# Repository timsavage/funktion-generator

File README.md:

##################
Funktion-generator
##################

AVR based function generator - Hardware + Firmware

Full project details at https://hackaday.io/project/19866

See sub folders for README docs on sub-components.

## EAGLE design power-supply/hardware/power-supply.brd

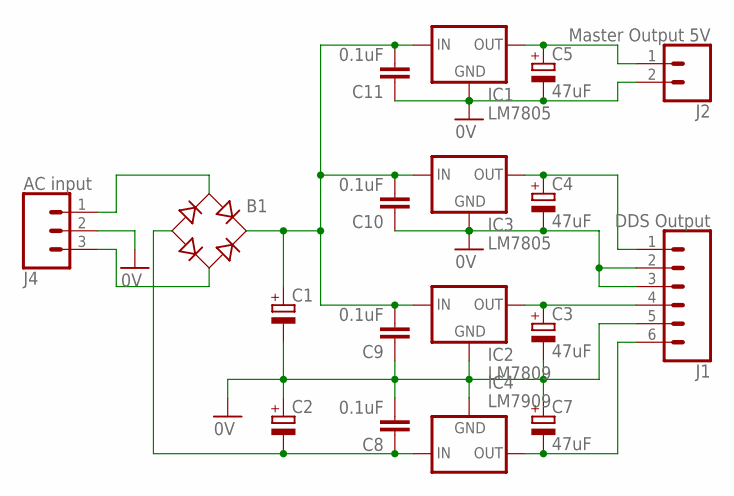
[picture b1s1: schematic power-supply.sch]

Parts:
B1: RB1A
C1, C2: CPOL-EUE7.5-16; E7,5-16
C3, C4, C7: 47uF; E5-6
C5: 47uF; E2,5-6
C8, C9, C10, C11: 0.1uF; C025-025X050
IC1, IC3: LM7805; 78XXS
IC2: LM7809; 78XXS
IC4: LM7909; 79XXS
J1: DDS Output; MOLEX-1X6
J2: Master Output 5V; MOLEX-1X2
J4: AC input; MOLEX-1X3

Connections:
0V: C1.-, C2.+, C3.-, C4.-, C5.-, C7.+, C8.2, C9.1, C10.1, C11.1, IC1.GND, IC2.GND, IC3.GND, IC4.GND, J1.2, J1.3, J1.5, J2.2, J4.2
5V-DDS: C4.+, IC3.OUT, J1.1
5V-MASTER: C5.+, IC1.OUT, J2.1
9V: C3.+, IC2.OUT, J1.4
-9V: C7.-, IC4.OUT, J1.6
unnamed: B1.+, C1.+, C9.2, C10.2, C11.2, IC1.IN, IC2.IN, IC3.IN
unnamed: B1.-, C2.-, C8.1, IC4.IN
unnamed: B1.AC2, J4.3
unnamed: B1.AC1, J4.1

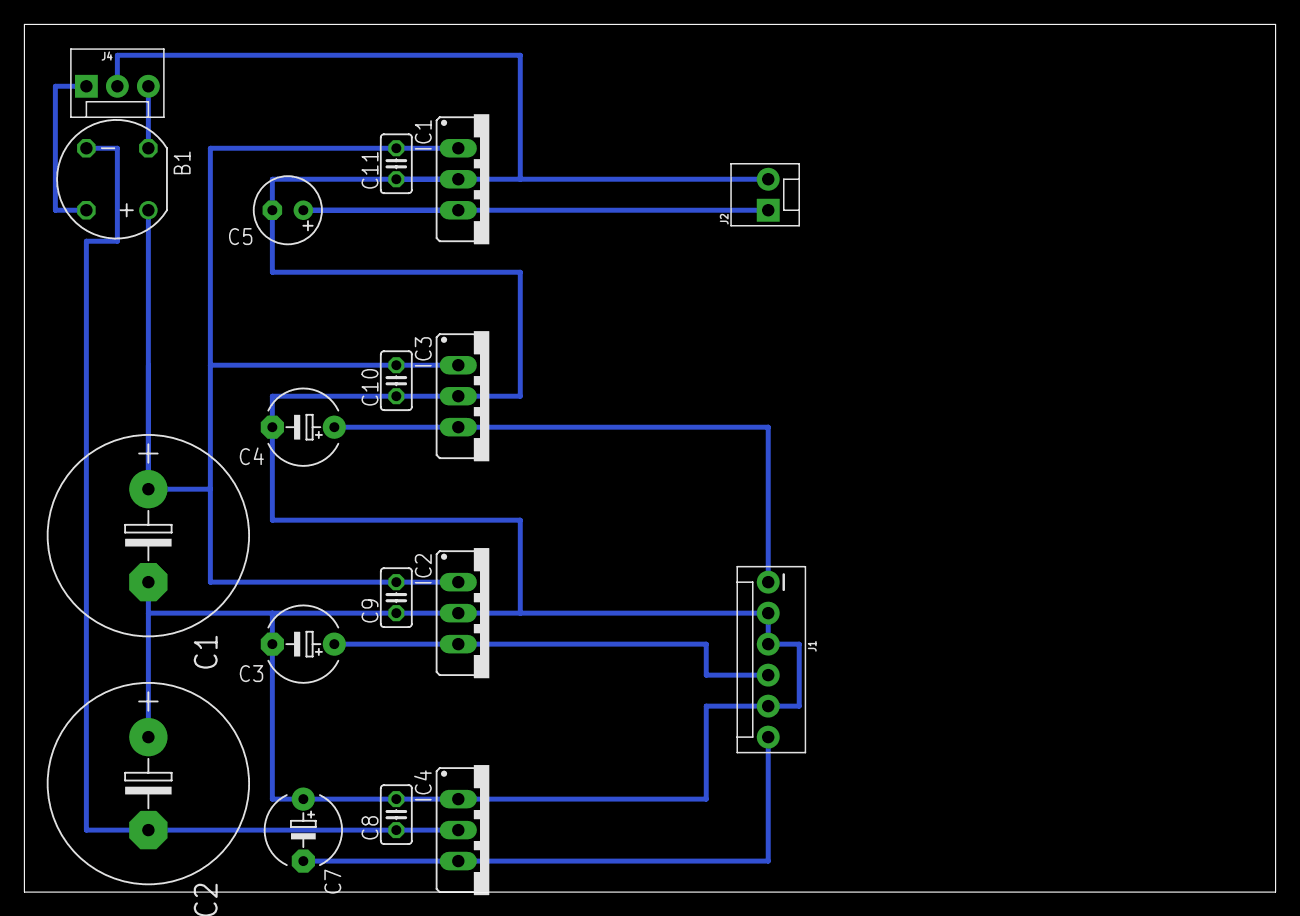
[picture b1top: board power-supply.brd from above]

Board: 2 copper layers, 102.5 x 71.1 mm, 18 parts (0 on the bottom side), 9 nets.

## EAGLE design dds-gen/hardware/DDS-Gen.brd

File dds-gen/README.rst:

#############
DDS Generator
#############

The DDS generate sub component is responsible for generating wave forms and providing amplitude and offset control. The heart of the component is an AVR microcontroller which is being overclocked to 30Mhz. The DDS generator is controlled via the I2C bus.

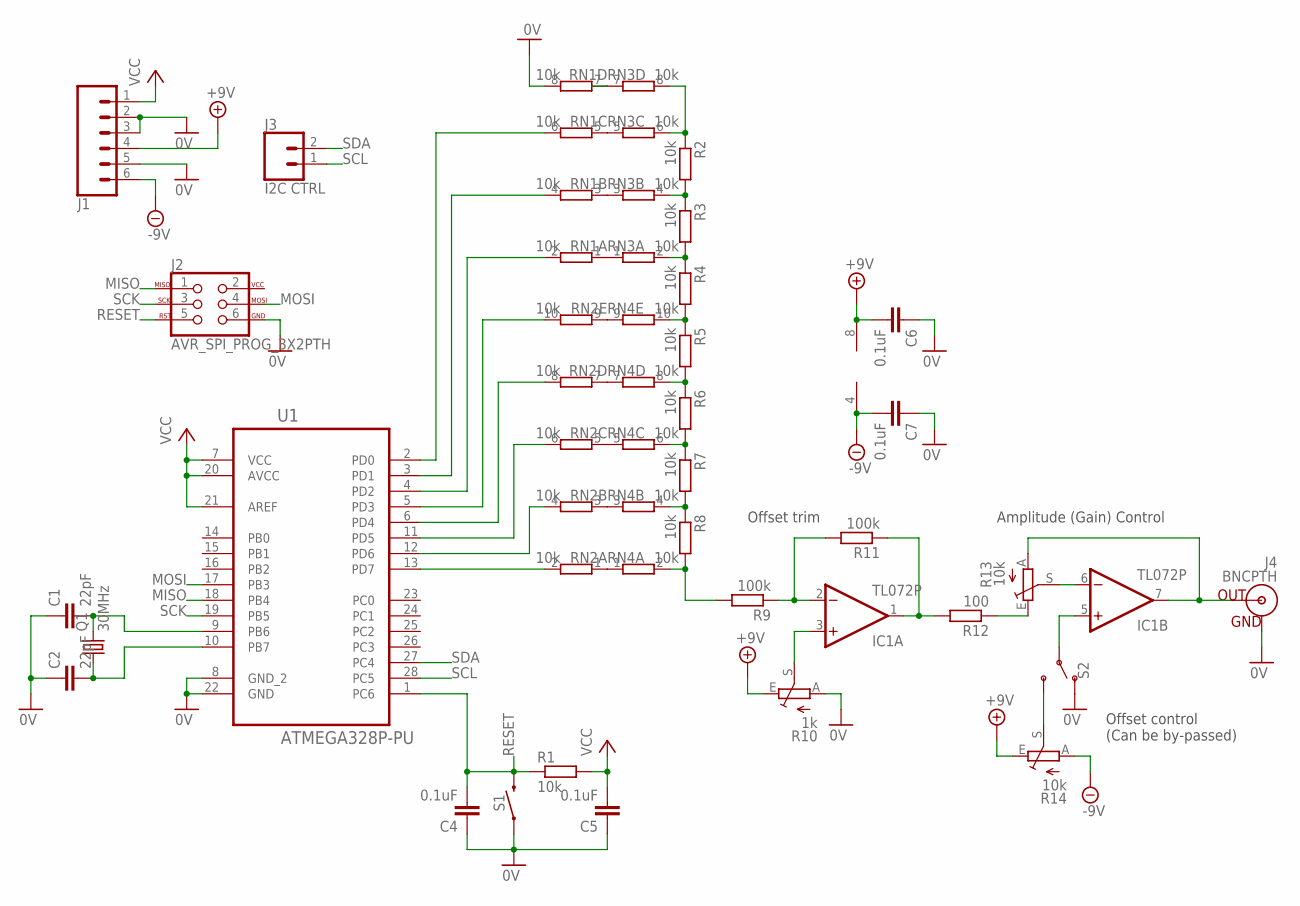
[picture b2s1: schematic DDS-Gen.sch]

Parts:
C1, C2: 22pF; C025-025X050
C4, C5, C6, C7: 0.1uF; C025-025X050
IC1: TL072P; DIL08
J1: CONN_06POLAR; MOLEX-1X6
J2: AVR_SPI_PROG_3X2PTH; 2X3
J3: I2C CTRL; MOLEX-1X2
J4: BNCPTH; BNC
Q1: 30MHz; HC49/S
R1, R2, R3, R4, R5, R6, R7, R8: 10k; 0204/5
R9: 100k; 0204/5
R10: 1k; S64W
R11: 100k; 0204V
R12: 100; 0207/12
R13, R14: 10k; CIP20C-6MM
RN1, RN2, RN3, RN4: 10k; SIL10
S1: MOMENTARY-SWITCH-SPST-PTH-6.0MM; TACTILE_SWITCH_PTH_6.0MM
S2: SWITCH-SPDT-PTH-11.6X4.0MM; SWITCH_SPDT_PTH_11.6X4.0MM
U1: ATMEGA328P-PU; DIP254P762X457-28

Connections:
0V: C1.1, C2.1, C4.1, C5.1, C6.1, C7.1, J1.2, J1.3, J1.5, J2.6, J4.GND, R10.A, RN1.8 (2), S1.1, S2.1 (O), U1.8 (GND_2), U1.22 (GND)
+9V: C6.2, IC1.8 (V+), J1.4, R10.E, R14.E
-9V: C7.2, IC1.4 (V-), J1.6, R14.A
MISO: J2.1, U1.18 (PB4)
MOSI: J2.4, U1.17 (PB3)
unnamed: C2.2, Q1.1, U1.10 (PB7)
unnamed: C1.2, Q1.2, U1.9 (PB6)
unnamed: IC1.3 (+IN), R10.S
unnamed: IC1.2 (-IN), R9.1, R11.2
unnamed: RN2.2, U1.13 (PD7)
unnamed: RN2.4 (2), U1.12 (PD6)
unnamed: RN2.6 (2), U1.11 (PD5)
unnamed: RN2.8 (2), U1.6 (PD4)
unnamed: RN2.10 (2), U1.5 (PD3)
unnamed: RN1.2, U1.4 (PD2)
unnamed: RN1.4 (2), U1.3 (PD1)
unnamed: RN1.6 (2), U1.2 (PD0)
unnamed: IC1.5 (+IN), S2.2
unnamed: R14.S, S2.3 (S)
unnamed: R12.1, R13.E
unnamed: IC1.1 (OUT), R11.1, R12.2
unnamed: IC1.6 (-IN), R13.S
unnamed: IC1.7 (OUT), J4.S (OUT), R13.A
unnamed: RN2.1, RN4.1
unnamed: RN2.3 (1), RN4.3 (1)
unnamed: RN2.5 (1), RN4.5 (1)
unnamed: RN2.7 (1), RN4.7 (1)
unnamed: RN2.9 (1), RN4.9 (1)
unnamed: RN1.1, RN3.1
unnamed: RN1.3 (1), RN3.3 (1)
unnamed: RN1.5 (1), RN3.5 (1)
unnamed: RN1.7 (1), RN3.7 (1)
unnamed: R2.1, RN3.6 (2), RN3.8 (2)
unnamed: R2.2, R3.1, RN3.4 (2)
unnamed: R3.2, R4.1, RN3.2
unnamed: R4.2, R5.1, RN4.10 (2)
unnamed: R5.2, R6.1, RN4.8 (2)
unnamed: R6.2, R7.1, RN4.6 (2)
unnamed: R7.2, R8.1, RN4.4 (2)
unnamed: R8.2, R9.2, RN4.2
RESET: C4.2, J2.5, R1.1, S1.3 (2), U1.1 (PC6)
SCK: J2.3, U1.19 (PB5)
SCL: J3.1, U1.28 (PC5)
SDA: J3.2, U1.27 (PC4)
VCC: C5.2, J1.1, R1.2, U1.7 (VCC), U1.20 (AVCC), U1.21 (AREF)

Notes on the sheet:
Offset trim
Amplitude (Gain) Control
Offset control (Can be by-passed)

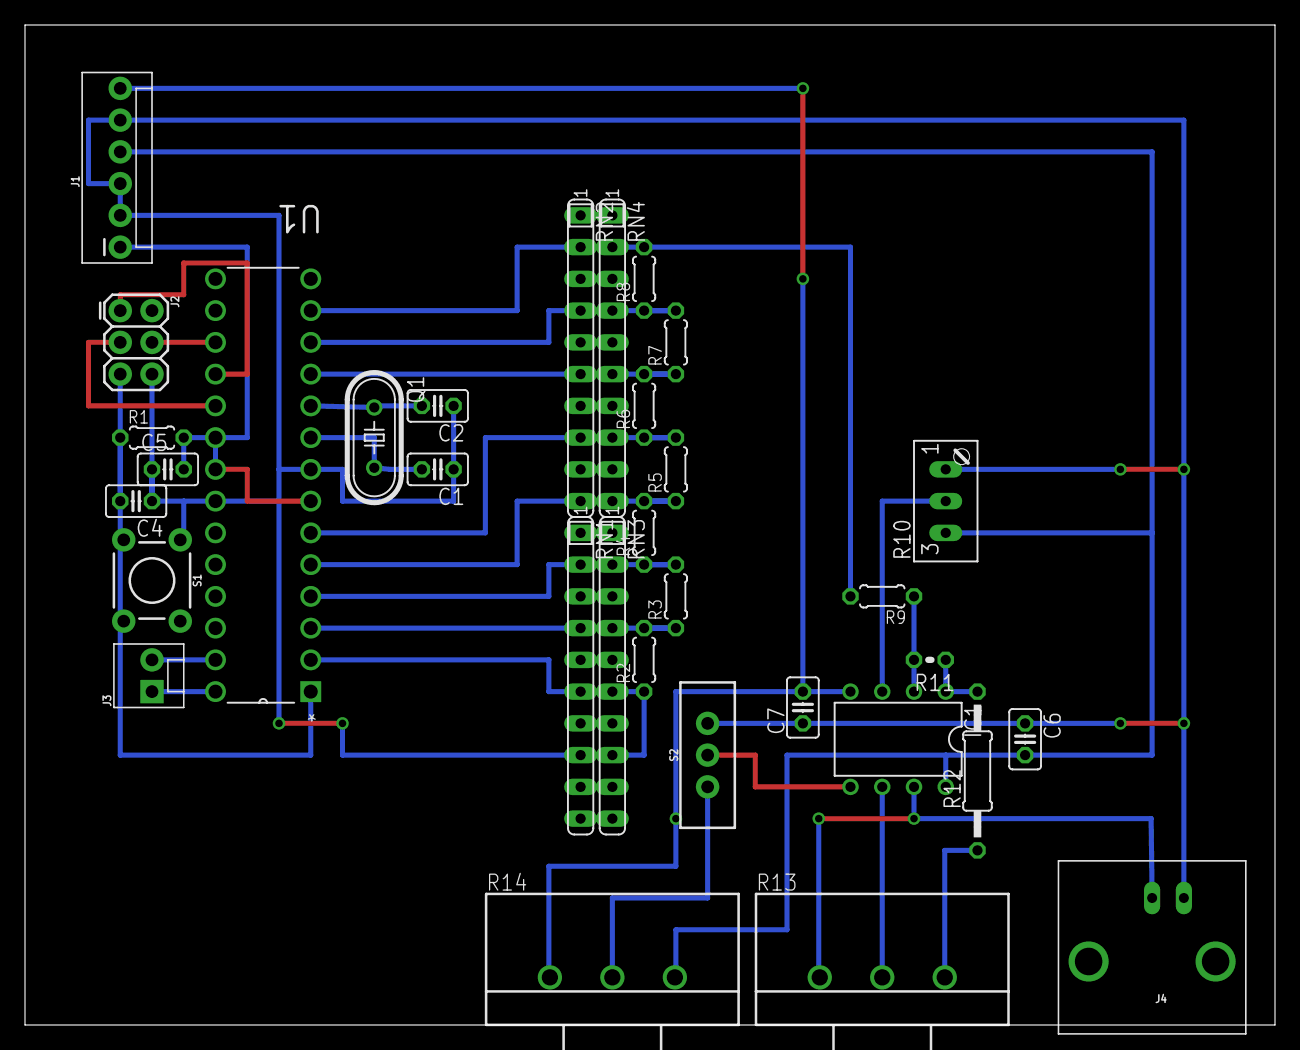
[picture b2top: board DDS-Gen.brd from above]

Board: 2 copper layers, 100.0 x 80.0 mm, 33 parts (0 on the bottom side), 45 nets.

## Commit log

2017-02-08 Initial dds gen
2017-02-08 Renamed to DDS Gen
2017-02-08 Removed old files
2017-02-08 Added wavetable generation script
2017-02-08 Added simulation end point for activating simulavr
2017-02-08 Added .gitignore
2017-02-09 Update format
2017-02-09 Added commands to control the device
2017-02-09 Added held state and code to deactive
2017-02-09 Updates to simplify the build and make process, fixed a couple of bugs and made the .S more compatible with .as
2017-02-28 Removed old items
2017-02-28 Migrated code from asmplay into this project repository
2017-02-28 Renamed ddsGen to dds-gen
2017-02-28 fixed name
2017-02-28 Added option to output constants, improved docs
2017-02-28 Rename README.md to README.rst
2017-02-28 Updated with correct file extensions
2017-03-02 Added DDS-Gen schematic
2017-03-03 Updates begin layout of board, switched to ganged resistors
2017-03-05 Layout tweaks and offset control.
    Added switchable offset control to output amplifier. Can be switched in or out.
    Tweak to layout so pots work in a natual manner (eg clockwise to increase amplitude)
2017-03-06 Added user interface directory
2017-03-06 Initial work for a waveform editor
2017-03-06 Updates to setup editor panel
2017-03-07 Re-arranged files and improved make process
2017-03-07 Ignore PyCharm files
2017-03-07 Make all and clean rules phony
2017-03-07 Added a editor MDI panel
2017-03-07 Updated window title
2017-03-07 Added requirements file
2017-03-07 Updated Schematic with slit power supply +-9V and 5V
2017-03-08 Added set of functions for generating and editing wave forms
2017-03-08 Added about dialog
2017-03-09 Added a WaveTable object to handle waves
    Object handles, load/save, and editing operations on the wave.
2017-03-09 Updated wave functions to be generators and modifiers
2017-03-10 Display wave, added user interface to generate and apply basic transforms to the waves
2017-03-10 Added ASM export, re-designed rendering to allow zoom easier and setup for mouse editing
2017-03-12 Added power-supply hardware design
2017-03-13 Split and improved export (formatter)
    Moved the ASM export functionality into a formatter object, decoupling
    export from the wave table.
    Added support for AVR Assembler (AVRASM2) in addition to GCC.
2017-03-13 Added wave table formatter for C
    Formatter desinged to output a wave table as C source.
2017-03-13 New menus and re-organised Waveform menu
    Added a menu for exporting to C
    Moved wave form generation into Waveform->Generate
    Added Waveform merge menu
2017-03-13 Added merge support, bug fixes
2017-03-13 Re-org of UI modules
2017-03-13 More menu opti
2017-03-13 Added run helper
2017-03-23 Create LICENSE
2017-04-04 ESP8266 version of my UI, includes wave table functions
2017-04-04 Added some manipulation methods
2017-04-06 Wave functions, simplification and undo.
    Added new wave functions, rectify_wave, normalise_wave and centre_wave. Each
    of these functions do as advertised.
    Some simplification to the internal code to allow addition of new wave functions
    easier, no longer does the same wave function need to be replicated in 4 places.
    This also leads into undo support. There is an unlimited undo buffer per wave
    editor. There is not currently support for redo, although this could be done
2017-04-06 A lot of work on wave_tables code.
    - Migrated all waves to files generated by wave editor on ESP8266 Filesystem.
    - Setup wifi and mDNS responder.
    - Started building out interface to DDS generator.
    - Started working on init process.
2017-04-07 Added a toolbar with icons. Added a View->Zoom menu
2017-04-07 Set icons (pyside-uic crashes if these are in ui files)
2017-04-07 Added simple zooming
2017-04-09 More work on the UI to display current state.\nInitilisation process is roughed out some refactors may be required to decouple parts of the code
2017-04-09 Set correct constants for zoom levels
2017-04-10 Started adding zeroconf device discovery
2017-04-10 Added initial device and discovery code
2017-04-10 Added mouse wheel zoom, wired up initial events from devices list
2017-04-13 Built out elements of the UI
2017-04-20 Initial work to migrate to center/offset work
2017-04-21 Added noise wave generator, redesign wave generation to be oriented around 0
2017-04-21 Expand and dupllicate output wave
2017-04-23 Updates to wave generation functions to generate more accurate waveforms

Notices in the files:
parts and their libraries:
SparkFun-Connectors: Licensing: Creative Commons ShareAlike 4.0 International - https://creativecommons.org/licenses/by-sa/4.0
